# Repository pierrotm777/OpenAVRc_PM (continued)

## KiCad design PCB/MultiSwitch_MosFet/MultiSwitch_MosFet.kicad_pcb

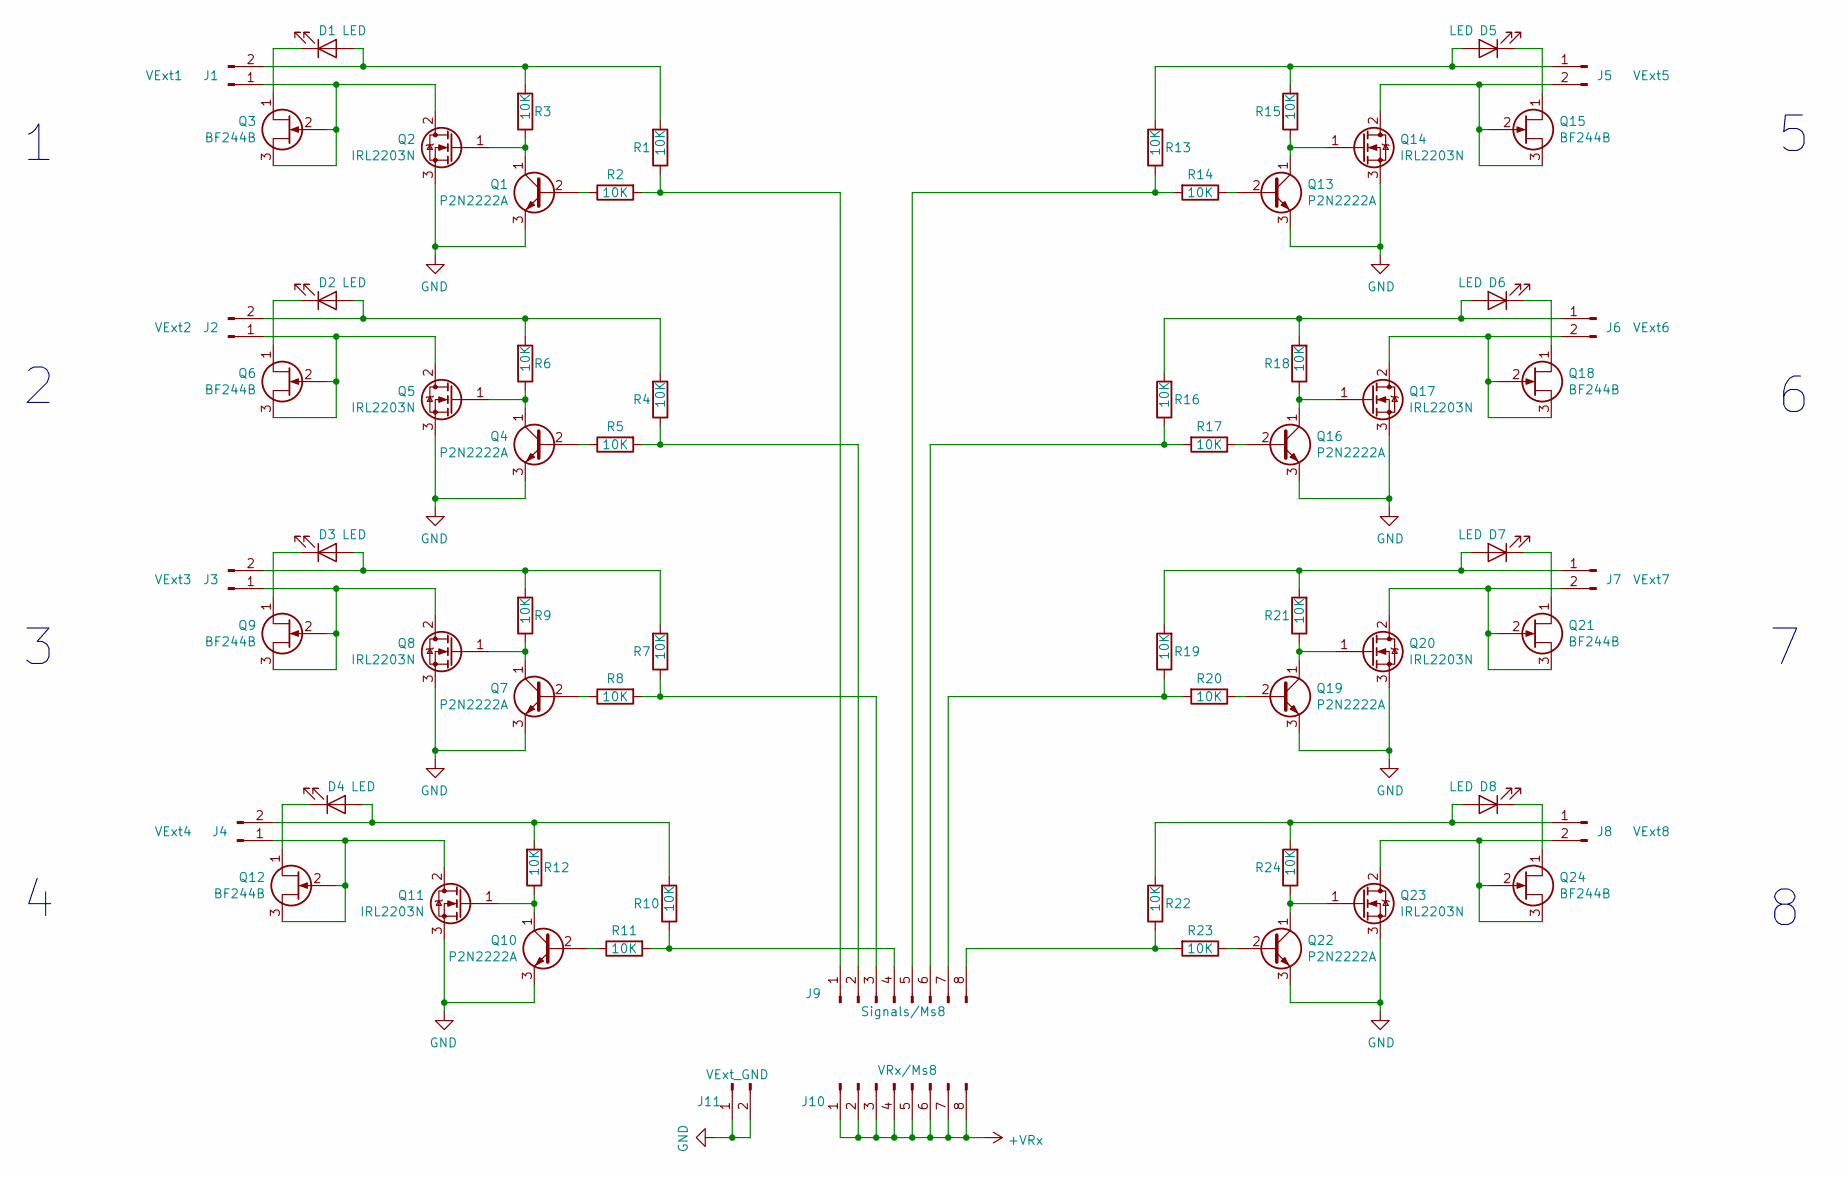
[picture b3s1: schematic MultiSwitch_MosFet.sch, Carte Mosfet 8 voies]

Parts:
D1, D2, D3, D4, D5, D6, D7, D8: LED; LED_D3.0mm
J1: VExt1; bornier2
J2: VExt2; bornier2
J3: VExt3; bornier2
J4: VExt4; bornier2
J5: VExt5; bornier2
J6: VExt6; bornier2
J7: VExt7; bornier2
J8: VExt8; bornier2
J9: Signals/Ms8; Pin_Header_Straight_1x08_Pitch2.54mm
J10: VRx/Ms8; Pin_Header_Straight_1x08_Pitch2.54mm
J11: VExt_GND; bornier2
Q1, Q4, Q7, Q10, Q13, Q16, Q19, Q22: P2N2222A; TO-92_Inline_Narrow_Oval
Q2, Q5, Q8, Q11, Q14, Q17, Q20, Q23: IRL2203N; TO-220_Vertical
Q3, Q6, Q9, Q12, Q15, Q18, Q21, Q24: BF244B; TO-92_Inline_Narrow_Oval
R1, R2, R3, R4, R5, R6, R7, R8, R9, R10, R11, R12, R13, R14, R15, R16, R17, R18, R19, R20, R21, R22, R23, R24: 10K; R_Axial_DIN0204_L3.6mm_D1.6mm_P2.54mm_Vertical

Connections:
+VRx: J10.1, J10.2, J10.3, J10.4, J10.5, J10.6, J10.7, J10.8
GND: J11.1, J11.2, Q1.3 (E), Q2.3 (S), Q4.3 (E), Q5.3 (S), Q7.3 (E), Q8.3 (S), Q10.3 (E), Q11.3 (S), Q13.3 (E), Q14.3 (S), Q16.3 (E), Q17.3 (S), Q19.3 (E), Q20.3 (S), Q22.3 (E), Q23.3 (S)
unnamed: D1.1 (K), Q3.1 (D)
unnamed: D1.2 (A), J1.2, R1.2, R3.2
unnamed: D2.1 (K), Q6.1 (D)
unnamed: D2.2 (A), J2.2, R4.2, R6.2
unnamed: D3.1 (K), Q9.1 (D)
unnamed: D3.2 (A), J3.2, R7.2, R9.2
unnamed: D4.1 (K), Q12.1 (D)
unnamed: D4.2 (A), J4.2, R10.2, R12.2
unnamed: D5.1 (K), Q15.1 (D)
unnamed: D5.2 (A), J5.1, R13.2, R15.2
unnamed: D6.1 (K), Q18.1 (D)
unnamed: D6.2 (A), J6.1, R16.2, R18.2
unnamed: D7.1 (K), Q21.1 (D)
unnamed: D7.2 (A), J7.1, R19.2, R21.2
unnamed: D8.1 (K), Q24.1 (D)
unnamed: D8.2 (A), J8.1, R22.2, R24.2
unnamed: J1.1, Q2.2 (D), Q3.2 (G), Q3.3 (S)
unnamed: J2.1, Q5.2 (D), Q6.2 (G), Q6.3 (S)
unnamed: J3.1, Q8.2 (D), Q9.2 (G), Q9.3 (S)
unnamed: J4.1, Q11.2 (D), Q12.2 (G), Q12.3 (S)
unnamed: J5.2, Q14.2 (D), Q15.2 (G), Q15.3 (S)
unnamed: J6.2, Q17.2 (D), Q18.2 (G), Q18.3 (S)
unnamed: J7.2, Q20.2 (D), Q21.2 (G), Q21.3 (S)
unnamed: J8.2, Q23.2 (D), Q24.2 (G), Q24.3 (S)
unnamed: J9.1, R1.1, R2.2
unnamed: J9.2, R4.1, R5.2
unnamed: J9.3, R7.1, R8.2
unnamed: J9.4, R10.1, R11.2
unnamed: J9.5, R13.1, R14.2
unnamed: J9.6, R16.1, R17.2
unnamed: J9.7, R19.1, R20.2
unnamed: J9.8, R22.1, R23.2
unnamed: Q1.1 (C), Q2.1 (G), R3.1
unnamed: Q1.2 (B), R2.1
unnamed: Q4.1 (C), Q5.1 (G), R6.1
unnamed: Q4.2 (B), R5.1
unnamed: Q7.1 (C), Q8.1 (G), R9.1
unnamed: Q7.2 (B), R8.1
unnamed: Q10.1 (C), Q11.1 (G), R12.1
unnamed: Q10.2 (B), R11.1
unnamed: Q13.1 (C), Q14.1 (G), R15.1
unnamed: Q13.2 (B), R14.1
unnamed: Q16.1 (C), Q17.1 (G), R18.1
unnamed: Q16.2 (B), R17.1
unnamed: Q19.1 (C), Q20.1 (G), R21.1
unnamed: Q19.2 (B), R20.1
unnamed: Q22.1 (C), Q23.1 (G), R24.1
unnamed: Q22.2 (B), R23.1

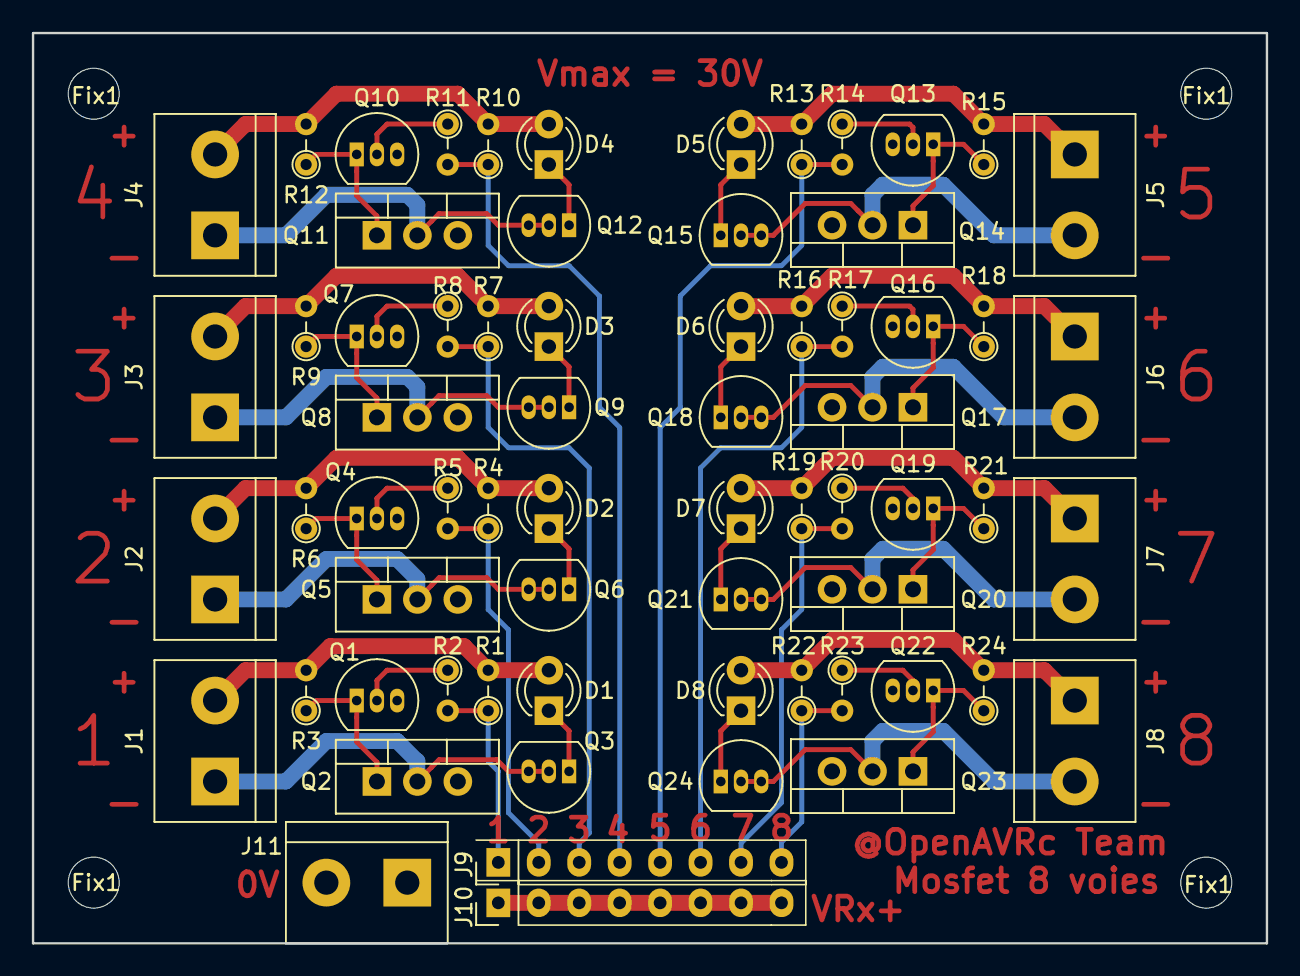
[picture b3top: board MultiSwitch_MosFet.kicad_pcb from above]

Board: 2 copper layers, 77.5 x 57.2 mm, 71 parts (0 on the bottom side), 50 nets.

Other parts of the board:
Fix1, Fix1#2, Fix1#3, Fix1#4: MountingHole_3.2mm_M3

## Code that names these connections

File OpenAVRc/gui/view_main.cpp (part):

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
#define displayVoltageOrAlarm() displayBattVoltage()

#define EVT_KEY_MODEL_MENU   EVT_KEY_LONG(KEY_RIGHT)
#define EVT_KEY_GENERAL_MENU EVT_KEY_LONG(KEY_LEFT)
#define EVT_KEY_TELEMETRY    EVT_KEY_LONG(KEY_DOWN)
#define EVT_KEY_STATISTICS   EVT_KEY_LONG(KEY_UP)
#define EVT_KEY_CONTEXT_MENU EVT_KEY_BREAK(KEY_MENU)
#define EVT_KEY_SHUTDOWN     EVT_KEY_LONG(KEY_EXIT)

void onMainViewMenu(const char *result)
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
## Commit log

2021-01-24 Update BtToSimulator_PPM.ino
    Add Joystick feature
2021-01-24 Add SCC feature for SBUS servo programmation
2021-01-25 Add PXX protocol
2022-02-16 Add power for CRSF
2022-02-20 remove files
2022-02-20 remove old files and hex
2022-02-20 add sx1276pag option
2022-03-12 update crsf
2022-04-10 Add V2 to FrskyX
2022-04-19 Several update
    -Update Frsky V1&V2
    -Update Hott
2022-04-23 Add Synchro On/Off & Telemetry
2022-04-23 Update HOTT_cc2500.c
    use g_model.rfOptionValue3 for failsafe
2022-04-23 Update HOTT_cc2500.c
    Update power management
2022-05-29 Update FRSKYX_cc2500.c
    Changes Frsky XV2
2022-09-17 Add Futaba PCM1024
2022-09-17 Update Makefile
2022-09-18 All update
    - source: Update pcm1024
    - desktop: add pcm1024 and sx1276
    - simu: add pcm1024
2022-09-20 Add Graupner S-PCM protocol
2022-09-20 Add Graupner S-PCM in Desktop
2022-09-24 Update hm10
2022-10-02 Updates
    - Work on HM10 and MLT BT05 Bluetooth
    - Add Gui Tracker
2022-10-13 Update Desktop
2022-10-22 Update PCM
2022-10-22 Updates for PCM
2022-11-15 Divers updates
    - update pcm
    - update mlink
    - update hott
2022-11-16 Update OpenAVRc.h
    Add SX1276 feature
2022-11-16 Add V911S protocol
2022-11-24 remove define error
